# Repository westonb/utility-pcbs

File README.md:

# utility-pcbs
Random small PCBs that do not need their own repo

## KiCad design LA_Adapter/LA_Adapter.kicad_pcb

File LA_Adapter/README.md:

# RTB2004 Logic Analyzer Adaptor 
A basic PCB to convert the RTB2004 LA pods into a 0.05" pitch pin header instead of flying leads. Resistor network is for 10k input impedance. To plug into the LA pod a standard 0.1" pitch header solders edgwise on to the exposed pads on the PCB. 

# Photos 
## Front 

## Back

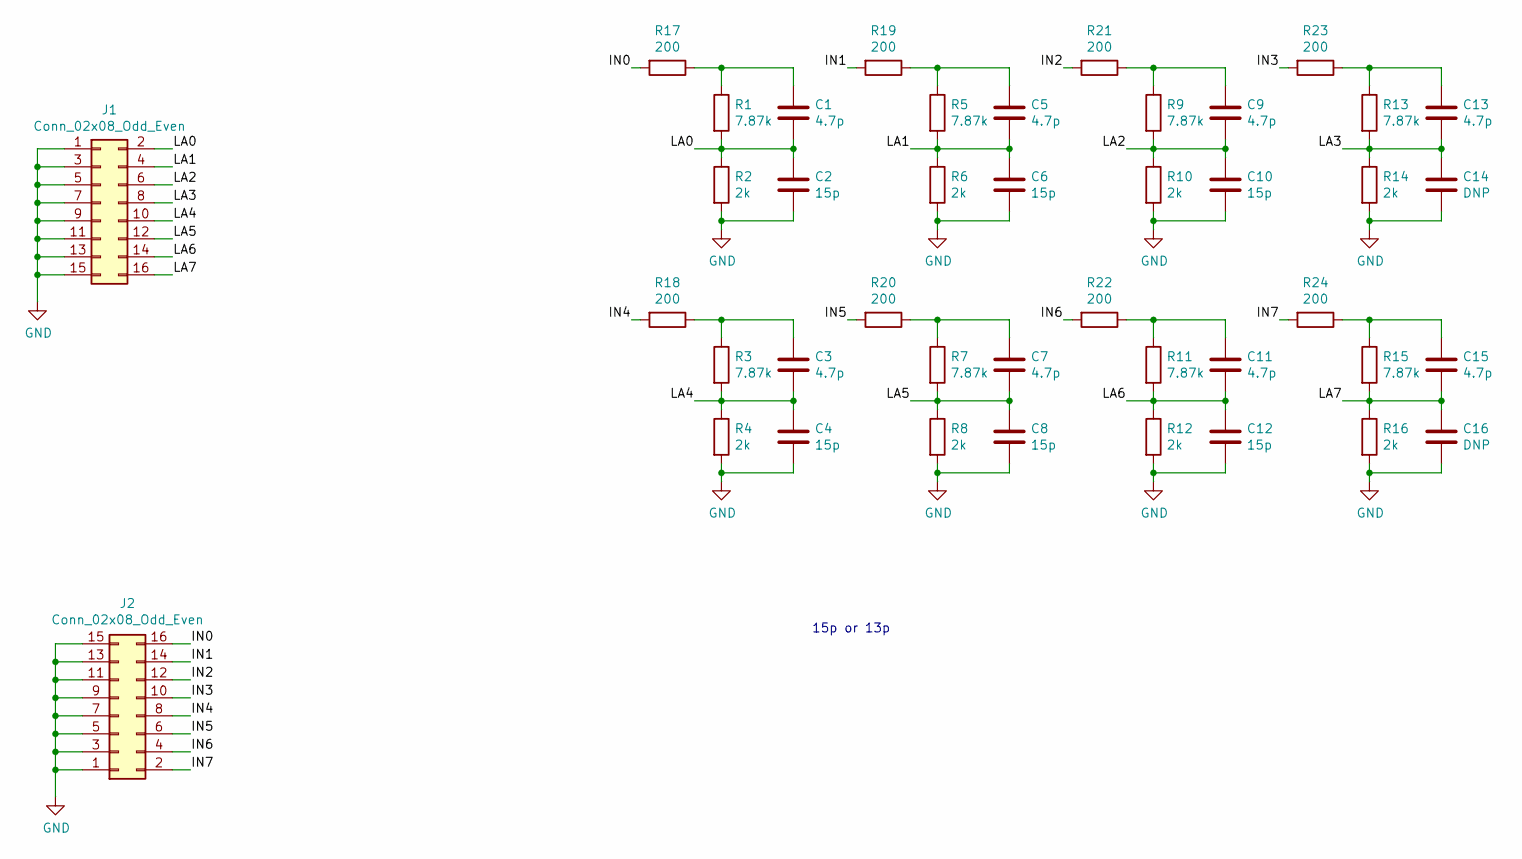
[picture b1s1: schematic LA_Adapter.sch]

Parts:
C1, C3, C5, C7, C9, C11, C13, C15: 4.7p; C_0402_1005Metric
C2, C4, C6, C8, C10, C12: 15p; C_0402_1005Metric
C14, C16: DNP; C_0402_1005Metric
J1: Conn_02x08_Odd_Even; pinheader_2x8_horizontal_mount_2.54mm
J2: Conn_02x08_Odd_Even; EHF-108-01-L-D
R1, R3, R5, R7, R9, R11, R13, R15: 7.87k; R_0402_1005Metric
R2, R4, R6, R8, R10, R12, R14, R16: 2k; R_0402_1005Metric
R17, R18, R19, R20, R21, R22, R23, R24: 200; R_0402_1005Metric

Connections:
/IN0: J2.16, R17.2
/IN1: J2.14, R19.2
/IN2: J2.12, R21.2
/IN3: J2.10, R23.2
/IN4: J2.8, R18.2
/IN5: J2.6, R20.2
/IN6: J2.4, R22.2
/IN7: J2.2, R24.2
/LA0: C1.2, C2.1, J1.2, R1.2, R2.1
/LA1: C5.2, C6.1, J1.4, R5.2, R6.1
/LA2: C9.2, C10.1, J1.6, R9.2, R10.1
/LA3: C13.2, C14.1, J1.8, R13.2, R14.1
/LA4: C3.2, C4.1, J1.10, R3.2, R4.1
/LA5: C7.2, C8.1, J1.12, R7.2, R8.1
/LA6: C11.2, C12.1, J1.14, R11.2, R12.1
/LA7: C15.2, C16.1, J1.16, R15.2, R16.1
GND: C2.2, C4.2, C6.2, C8.2, C10.2, C12.2, C14.2, C16.2, J1.1, J1.3, J1.5, J1.7, J1.9, J1.11, J1.13, J1.15, J2.1, J2.3, J2.5, J2.7, J2.9, J2.11, J2.13, J2.15, R2.2, R4.2, R6.2, R8.2, R10.2, R12.2, R14.2, R16.2
unnamed: C1.1, R1.1, R17.1
unnamed: C3.1, R3.1, R18.1
unnamed: C5.1, R5.1, R19.1
unnamed: C7.1, R7.1, R20.1
unnamed: C9.1, R9.1, R21.1
unnamed: C11.1, R11.1, R22.1
unnamed: C13.1, R13.1, R23.1
unnamed: C15.1, R15.1, R24.1

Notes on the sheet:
15p or 13p

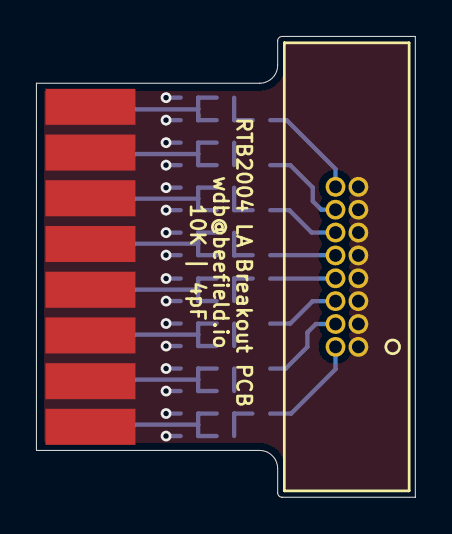
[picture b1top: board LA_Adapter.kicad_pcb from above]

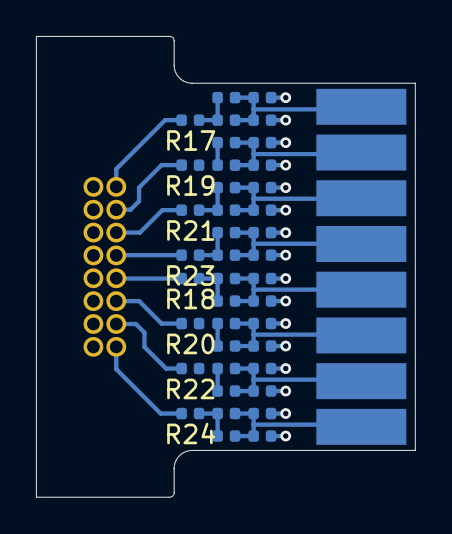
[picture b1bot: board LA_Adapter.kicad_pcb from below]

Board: 2 copper layers, 21.0 x 25.6 mm, 42 parts (40 on the bottom side), 25 nets.

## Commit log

2020-10-18 added git ignore for kicad
2020-10-18 added LA adaptor PCB
